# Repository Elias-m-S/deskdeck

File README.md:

<h1 align="center">DeskDeck</h1>

<p align="center">
  <b>An ESP32-S3 macro pad that lives under the edge of your desk:</b><br>
  per-app volume knobs, a sit/stand desk controller with a laser height sensor, and a Home Assistant link.<br>
  Firmware, PCB and 3D-printed enclosure, all in one repository.
</p>

<p align="center">

</p>

---

## What it does

- **Per-app volume on two knobs.** Each EC11 encoder is bound to an application (Discord, a game, the browser, the master output). A small host daemon talks to PipeWire/PulseAudio over the USB serial port; the OLED shows name, level and a bar for each knob. Press a knob to mute. Without the daemon, the master knob still works through plain USB media keys.
- **Four MX keys.** Keyboard shortcuts over USB HID (e.g. `Super+1`), or special actions: one key toggles the desk between sitting and standing, one triggers a light scene in Home Assistant.
- **Sit/stand desk controller.** Two optocouplers sit in parallel with the desk's own buttons, galvanically isolated from the ESP. A VL53L1X time-of-flight sensor measures the height to the floor. Profiles, calibration and the learned coasting distance are stored in flash. The drive logic is a pure state machine with hard safety limits and a host-side simulation test.
- **Home Assistant over Wi-Fi + MQTT.** The device announces itself through MQTT discovery: a desk-height sensor, sit/stand buttons and a key trigger. HA can push short messages to the display.
- **No buttons needed to flash.** The firmware reboots itself into the ROM bootloader on request; `flash.sh` builds, flashes and restarts in one go.
- **Two mechanical desk buttons** on the same board are wired straight to the desk, so the desk always works, even with the ESP unpowered.

## Gallery

| PCB, bottom side (ESP32-S3 SuperMini, optocouplers, terminal block) | Schematic |
|---|---|
|  |  |

| Enclosure, exploded | Section through display, encoder and keys |
|---|---|
|  |  |

| Two-colour keycaps (3MF, generated from Lucide icons) |
|---|
|  |

## How it works

```mermaid
flowchart LR
    subgraph DeskDeck["DeskDeck (ESP32-S3, FreeRTOS)"]
        direction LR
        IN[input<br/>keys + encoders<br/>PCNT, debounce] -->|events| UI[ui<br/>state machine<br/>menus, NVS]
        UI --> HID[usb_hid<br/>keyboard + media keys]
        UI --> HL[host_link<br/>text protocol over CDC]
        UI --> DISP[display<br/>SH1106 128x64]
        TOF[tof<br/>VL53L1X 20 Hz] --> DESK[desk<br/>drive logic + safety]
        UI --> DESK
        HA[ha_link<br/>Wi-Fi + MQTT]
        HA <--> UI
        DESK --> HA
    end
    HID -->|USB HID| PC[(PC)]
    HL <-->|USB CDC| DAEMON[host daemon<br/>pactl / PipeWire]
    DAEMON --- PC
    DESK -->|2x PC817| MOTOR[desk control box]
    HA <-->|MQTT| HASS[Home Assistant]
```

Every block is its own FreeRTOS task. All UI state belongs to exactly one task and is fed through a single event queue, so there is no shared mutable state to lock.

**Per-app volume.** The device sends `@ADJ +2 Discord` or `@MUTE Discord` over the CDC port. The daemon matches the name against running audio streams (`application.name` / binary) and applies it with `pactl`; it answers with `@LVL <percent> <muted> <active> <name>` and the list of selectable targets, which the device shows in its menu. Levels for apps that are not running are remembered and applied as soon as a stream appears. Protocol: [`firmware/main/host_link.h`](firmware/main/host_link.h).

**Desk control.** Target height = sensor distance + calibrated offset. The logic in [`desk_logic.c`](firmware/main/desk_logic.c) has no hardware access and is exercised against a simulated desk in [`test/desk_sim.c`](firmware/test/desk_sim.c): accuracy after learning the coasting distance, plus every abort case. Safety rules:

| Rule | Value |
|---|---|
| Maximum time per profile move | 20 s |
| After a 2 s spin-up the desk must move per second at least | 8 mm in the right direction |
| Movement in the wrong direction aborts after | 15 mm |
| No fresh sensor reading for | 300 ms -> abort |
| Any user input while moving | stops immediately |
| Outputs | off at boot, never both on at once, pulled down in hardware |

**Home Assistant.** MQTT discovery creates a device *DeskDeck* with the entities desk height (`deskdeck/desk/height`), sit/stand buttons (`deskdeck/cmd/desk`) and a trigger for key 4 (`deskdeck/key/4`). `deskdeck/cmd/toast` shows a short text on the display. Topics: [`firmware/main/ha_link.h`](firmware/main/ha_link.h).

## Repository layout

| Directory | Contents | Details |
|---|---|---|
| [`firmware/`](firmware/) | ESP-IDF project: input, UI, display driver, VL53L1X driver, desk logic, USB composite device, MQTT | [firmware/README.md](firmware/README.md) |
| [`host/`](host/) | Python daemon for per-app volume (PipeWire/PulseAudio via `pactl`), systemd user unit | [host/README.md](host/README.md) |
| [`hardware/`](hardware/) | KiCad project, Gerber ZIP for JLCPCB, BOM, schematic PDF, Python generator that builds schematic + board from one data file | [hardware/README.md](hardware/README.md) |
| [`enclosure/`](enclosure/) | Parametric FreeCAD enclosure (reads the board data from `hardware/`), print-ready STL, two-colour keycaps | [enclosure/README.md](enclosure/README.md) |
| [`docs/images/`](docs/images/) | Renders used in the READMEs | |

## Build one

1. **PCB.** Upload [`hardware/fabrication/deskdeck-gerber-jlcpcb.zip`](hardware/fabrication/) to JLCPCB or any 2-layer fab (119 x 62 mm, 1.6 mm, HASL). Parts are all through-hole, see the [BOM](hardware/fabrication/bom.csv) and the [soldering order](hardware/README.md#assembly-order).
2. **Enclosure.** Print the five STL files in [`enclosure/stl/`](enclosure/stl/) (PETG, no supports) and the keycaps in [`enclosure/keycaps/`](enclosure/keycaps/). Assembly and the drill template for the desk are in [enclosure/README.md](enclosure/README.md).
3. **Firmware.**
   ```bash
   cd firmware
   cp main/secrets.h.example main/secrets.h   # Wi-Fi/MQTT credentials, or leave empty
   idf.py set-target esp32s3 && idf.py build
   ./flash.sh                                   # or: idf.py flash
   ```
   First flash of a blank board: hold BOOT, tap RST, release BOOT, then flash. From then on `flash.sh` reboots the device into the bootloader by itself.
4. **Host daemon** (Linux with PipeWire or PulseAudio):
   ```bash
   sudo apt install python3-serial pulseaudio-utils
   host/install.sh                              # systemd user service, starts at login
   ```
   Then edit `~/.config/deskdeck/config.json` to map knob targets to your applications (`host/deskdeck_daemon.py --list` shows what is playing).
5. **Home Assistant.** Point `MQTT_URI` in `secrets.h` at your broker. The device appears automatically. Create an automation on the key-4 trigger and, optionally, publish feedback to `deskdeck/cmd/toast`.

## Hardware at a glance

| Part | Role |
|---|---|
| ESP32-S3 SuperMini | MCU, native USB (TinyUSB composite: HID + CDC), Wi-Fi |
| 1.3" SH1106 OLED, I2C | Display, flush with the lid |
| 2x EC11 rotary encoder with push button | Volume / menu, mute |
| 6x Cherry MX compatible switches | 4 macro keys + 2 purely mechanical desk buttons |
| VL53L1X (TOF400C module) | Height to the floor, 20 Hz, median filtered, narrowed ROI |
| 2x PC817 optocoupler, 470 R + 10 k | Isolated desk UP/DOWN outputs |
| 3-pole screw terminal | Desk control box (VCC, M1, M2) |

Pin map (all inputs active-low with internal pull-ups):

| Function | GPIO |
|---|---|
| Encoder 1 A / B / switch | 1 / 2 / 4 |
| Encoder 2 A / B / switch | 9 / 10 / 11 |
| MX keys 1-4 | 5, 6, 7, 8 |
| I2C SDA / SCL (OLED + sensor) | 12 / 13 |
| Desk UP / DOWN (optocoupler LEDs) | 44 / 3 |
| On-board WS2812 status LED | 48 |

Everything configurable (pins, key map, encoder targets, desk limits, timings) lives in [`firmware/main/config.h`](firmware/main/config.h).

## Safety

The desk side of the board carries the desk's own control voltage. It is isolated from the ESP by the optocouplers, a copper keep-out and a DRC rule enforcing 0.8 mm clearance; there is no shared ground. Keep it that way. Start with `DESK_DRY_RUN 1` in `config.h`: the complete logic runs, including the sensor, but the outputs never switch. Only after you have verified the wiring, set it to `0` and calibrate the height once from the menu.

## Notes

- The strings shown on the OLED and the Home Assistant entity names are German, the author's UI language. They are plain literals in `ui.c`, `desk_logic.c`, `tof.c` and `ha_link.c`.
- Mechanical dimensions (SuperMini footprint, OLED module, TOF400C cap, EC11 clone body) were measured on the actual parts; the READMEs list what to re-measure before ordering or printing.
- Boards fabricated before the project was renamed carry the silkscreen "ESP32-S3 Stream Deck v2". They are electrically identical to this revision.

## License

MIT, see [LICENSE](LICENSE). It also lists the third-party pieces: the Adafruit 5x7 font, the register sequence from ST's VL53L1X Ultra Lite Driver, Lucide icon outlines on the keycaps, and symbols/footprints from the KiCad libraries.

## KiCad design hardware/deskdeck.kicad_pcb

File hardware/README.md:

# PCB (rev 2)

2-layer board, **119 x 62 mm**, through-hole parts only (everything is hand-solderable). KiCad 7 format, opens in KiCad 7 to 10 (newer versions ask to convert once).

| Bottom side | Top side |
|---|---|
|  |  |

```
Top side                                           Bottom side (top strip + behind the OLED)
┌──────────────────────────────────────────┐       ESP32-S3 SuperMini on female headers (USB-C towards the top
│ ┌────────┐ (E1)  [1]  [3]  [▲]            │       edge, BOOT/RST reachable from the back), 2x PC817, 4 resistors,
│ │  OLED  │                                │       sensor header (1x4), desk screw terminal (3-pole)
│ └────────┘ (E2)  [2]  [4]  [▼]            │
└──────────────────────────────────────────┘
```

## Desk interface

The desk switches **high side**: the original hand switch connects `VCC` to `M1` (up) or `M2` (down). The desk buttons ▲▼ and the optocoupler outputs sit **in parallel** on these lines, so the buttons always work, even without the ESP.

| Terminal J3 | Desk line | PC817 | Button |
|---|---|---|---|
| 1 `UP` | M1 | U2 pin 3 (emitter) | SW7 |
| 2 `DOWN` | M2 | U3 pin 3 (emitter) | SW8 |
| 3 `VCC` | VCC | U2 + U3 pin 4 (collector) | SW7 + SW8 |

The nets `DESK_UP`, `DESK_DN`, `DESK_VCC` are **galvanically isolated from the ESP**. They belong to the net class `Desk`, and the DRC rule in `deskdeck.kicad_dru` demands **>= 0.8 mm** clearance to everything on the ESP side. There is deliberately no GND pour in the desk area.

rev 1 -> rev 2: `DESK_GND` -> `DESK_VCC`, pins 3 and 4 swapped on U2/U3, isolation clearance 0.25 -> 0.8 mm, silkscreen with >= 0.15 mm line width.

## Verification status (rev 2)

- Schematic netlist, board and `generator/design.py` compared automatically (`generator/check.py`): **identical**
- DRC: **0 unconnected items, 0 clearance, courtyard or silkscreen errors** (tracks 0.3 mm, clearance 0.25 mm, vias 0.7/0.35 mm). KiCad 8+ additionally reports the SuperMini socket pins inside the OLED courtyard, which is intentional: those pins are clipped flush, see the assembly order.
- Isolation clearance desk <-> ESP measured (`generator/iso.py`): **0.80 mm**
- GPIOs cross-checked against `firmware/main/config.h`: encoders 1/2/4 and 9/10/11, keys 5-8, I2C 12/13, desk 44/3
- Gerbers rendered independently and inspected; drill files separated (PTH/NPTH)
- Tested on a breadboard: optocouplers, desk buttons in parallel, manual drive
- Measured on the real parts: SuperMini pinout (`TX RX 1-7` / `5V GND 3V3 13-8`, USB up), row pitch ~15.2 mm, OLED pins `GND VCC SCL SDA`

## Ordering (JLCPCB or similar)

1. Upload `fabrication/deskdeck-gerber-jlcpcb.zip`
2. Defaults: 2 layers, 1.6 mm, HASL, any colour
3. The size is detected from the file (119 x 62 mm)

## Parts

See [`fabrication/bom.csv`](fabrication/bom.csv). Apart from the modules (SuperMini, OLED, TOF400C, encoders, switches) you only need small parts: 2x female header 1x9, 2x pin header 1x4 (OLED + sensor), 3-pole screw terminal 5.08 mm, 2x 470 R, 2x 10 k, M3 screws/stand-offs.

## Assembly order

Flat parts first so the board lies flat while soldering:

1. **Bottom side:** resistors R1-R4 -> PC817 (notch/dot = pin 1, see silkscreen) -> pin header J2 -> screw terminal J3 (cable entry towards the top edge)
2. **Bottom side:** 1x9 female headers for the SuperMini. Tip: keep the module plugged in while soldering the headers, then they sit straight.
3. **Top side, under the OLED:** clip the 6 lowest pins of the SuperMini headers (the bottom 3 of each row) flush and cover the spot with Kapton tape. The OLED later sits only ~2.5 mm above the board.
4. **Top side:** solder the OLED **directly** (no socket, so the glass ends up flush with the lid): a normal 1x4 pin header, plastic spacer resting on the board, clip the short pin ends flush on top of the OLED. Align the OLED level, solder one pin, check, then the rest.
5. **Top side:** encoders, finally the MX switches (best with the lid clipped on as a switch plate, then they sit exactly)

**Desk cable:** 3 wires to J3: `UP` = M1, `DOWN` = M2, `VCC` = desk VCC.
**Sensor:** 4-wire cable from J2 to the TOF400C, by label: `3V3`->`VIN`, `GND`->`GND`, `SDA`->`SDA`, `SCL`->`SCL`.

## Files

```
deskdeck.*        KiCad project (schematic, board, project symbol/footprint libraries)
fabrication/      Gerber ZIP, schematic PDF, BOM
generator/        Python scripts that generate schematic + board from design.py (KiCad 7 + Freerouting)
```

The enclosure ([`../enclosure/`](../enclosure/)) imports `generator/design.py` for the board outline, holes and part positions.

### Generator

`design.py` holds the circuit as data: parts, footprints, positions and the pin-to-net map. `gen_sch.py` and `gen_pcb.py` turn it into a schematic and an unrouted board (so both match by construction), `route.py` runs Freerouting and imports the result with GND pours, `check.py` runs DRC and compares schematic, board and `design.py`, `iso.py` measures the isolation clearance. `gen_pcb.py`/`route.py` use the KiCad 7 pcbnew Python API. If you continue by hand in KiCad, the KiCad files are the source from then on, not `design.py`.

Boards fabricated before the project was renamed carry the silkscreen "ESP32-S3 Stream Deck v2"; the copper is identical.

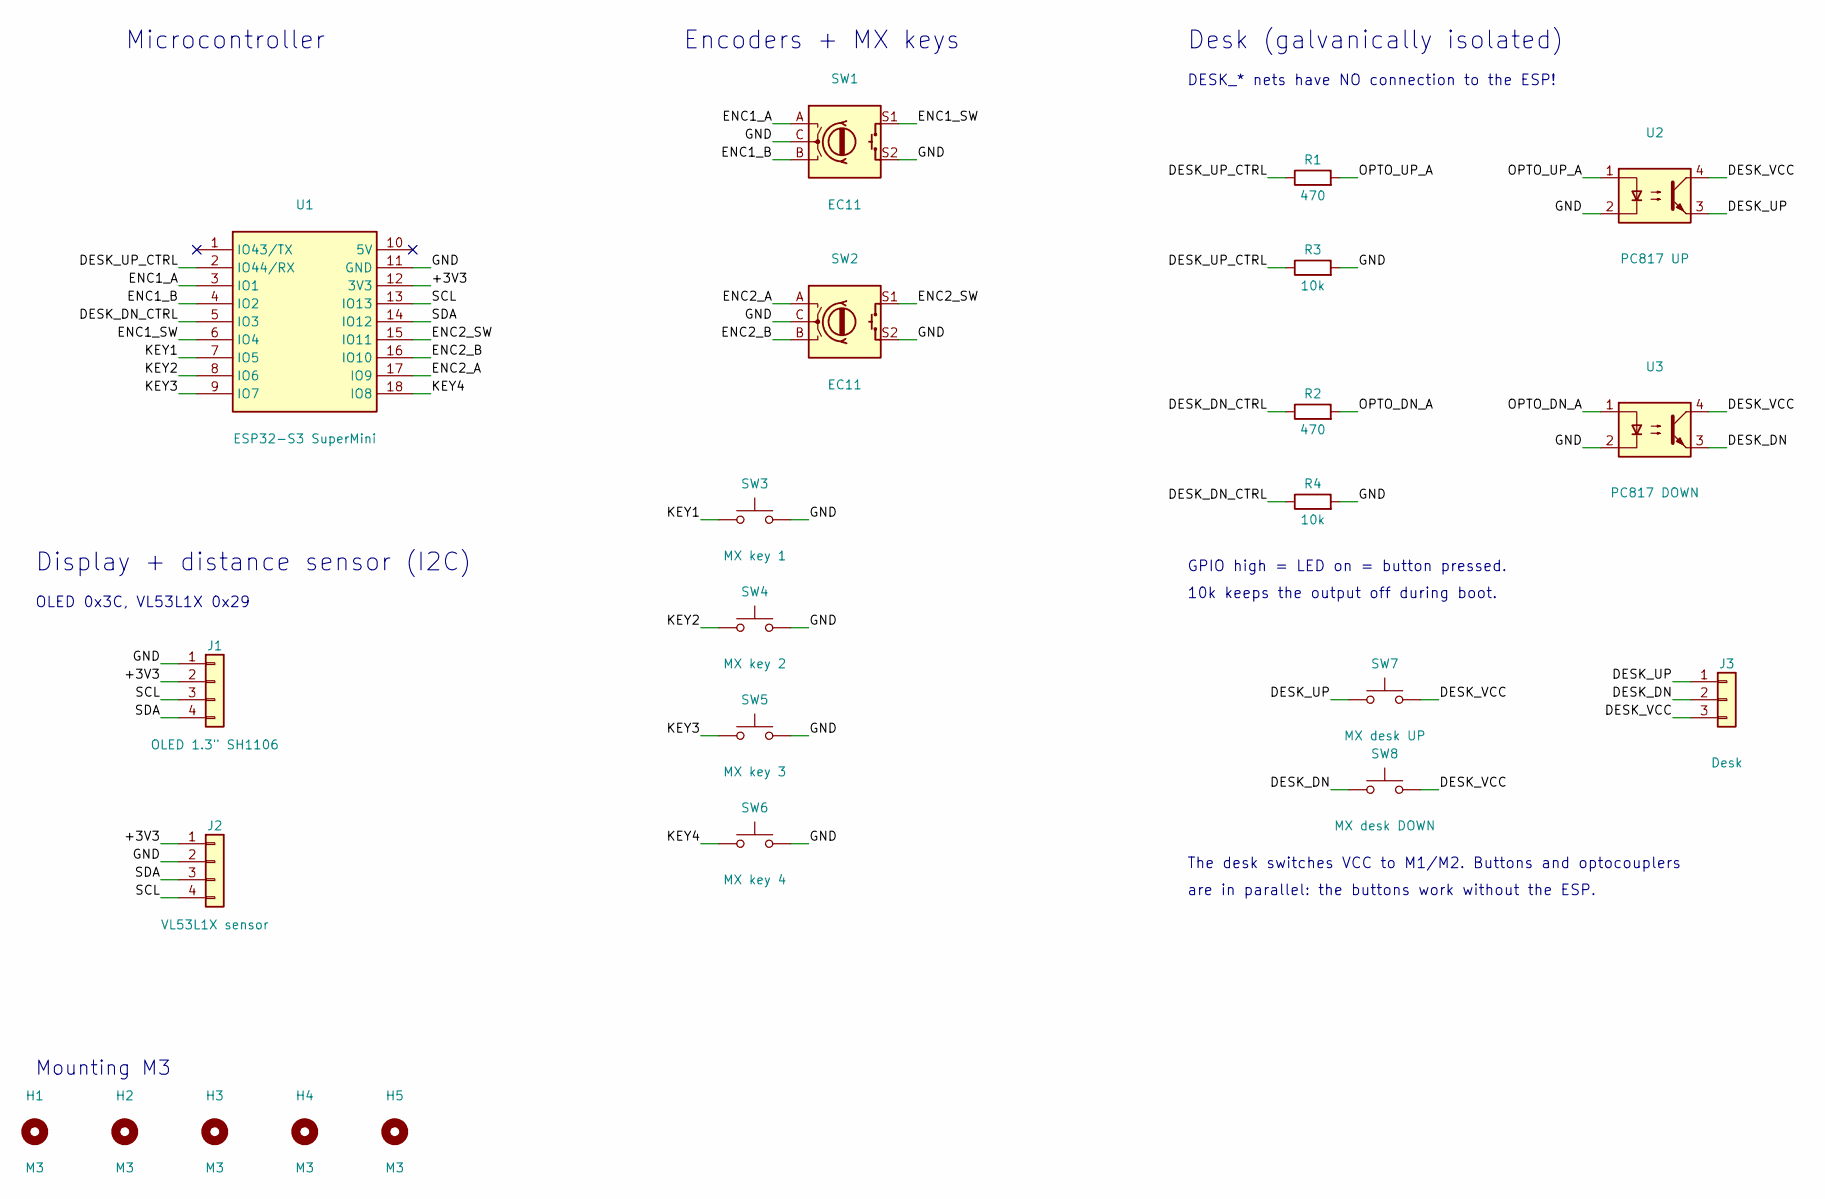
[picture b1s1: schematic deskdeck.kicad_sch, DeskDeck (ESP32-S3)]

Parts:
H1, H2, H3, H4, H5: M3; MountingHole_3.2mm_M3
J1: OLED 1.3" SH1106; OLED_1.3in_I2C_Socket
J2: VL53L1X sensor; PinHeader_1x04_P2.54mm_Vertical
J3: Desk; TerminalBlock_Phoenix_MKDS-1,5-3-5.08_1x03_P5.08mm_Horizont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
R1, R2: 470; R_Axial_DIN0207_L6.3mm_D2.5mm_P7.62mm_Horizontal
R3, R4: 10k; R_Axial_DIN0207_L6.3mm_D2.5mm_P7.62mm_Horizontal
SW1, SW2: EC11; RotaryEncoder_Alps_EC11E-Switch_Vertical_H20mm
SW3: MX key 1; SW_Cherry_MX_1.00u_PCB
SW4: MX key 2; SW_Cherry_MX_1.00u_PCB
SW5: MX key 3; SW_Cherry_MX_1.00u_PCB
SW6: MX key 4; SW_Cherry_MX_1.00u_PCB
SW7: MX desk UP; SW_Cherry_MX_1.00u_PCB
SW8: MX desk DOWN; SW_Cherry_MX_1.00u_PCB
U1: ESP32-S3 SuperMini; ESP32-S3_SuperMini_Socket
U2: PC817 UP; DIP-4_W7.62mm
U3: PC817 DOWN; DIP-4_W7.62mm

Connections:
+3V3: J1.2, J2.1, U1.12 (3V3)
DESK_DN: J3.2, SW8.1, U3.3
DESK_DN_CTRL: R2.1, R4.1, U1.5 (IO3)
DESK_UP: J3.1, SW7.1, U2.3
DESK_UP_CTRL: R1.1, R3.1, U1.2 (IO44/RX)
DESK_VCC: J3.3, SW7.2, SW8.2, U2.4, U3.4
ENC1_A: SW1.A, U1.3 (IO1)
ENC1_B: SW1.B, U1.4 (IO2)
ENC1_SW: SW1.S1, U1.6 (IO4)
ENC2_A: SW2.A, U1.17 (IO9)
ENC2_B: SW2.B, U1.16 (IO10)
ENC2_SW: SW2.S1, U1.15 (IO11)
GND: J1.1, J2.2, R3.2, R4.2, SW1.C, SW1.S2, SW2.C, SW2.S2, SW3.2, SW4.2, SW5.2, SW6.2, U1.11 (GND), U2.2, U3.2
KEY1: SW3.1, U1.7 (IO5)
KEY2: SW4.1, U1.8 (IO6)
KEY3: SW5.1, U1.9 (IO7)
KEY4: SW6.1, U1.18 (IO8)
OPTO_DN_A: R2.2, U3.1
OPTO_UP_A: R1.2, U2.1
SCL: J1.3, J2.4, U1.13 (IO13)
SDA: J1.4, J2.3, U1.14 (IO12)

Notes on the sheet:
Microcontroller
Display + distance sensor (I2C)
OLED 0x3C, VL53L1X 0x29
Encoders + MX keys
Desk (galvanically isolated)
DESK_* nets have NO connection to the ESP!
GPIO high = LED on = button pressed.
10k keeps the output off during boot.
The desk switches VCC to M1/M2. Buttons and optocouplers
are in parallel: the buttons work without the ESP.
Mounting M3

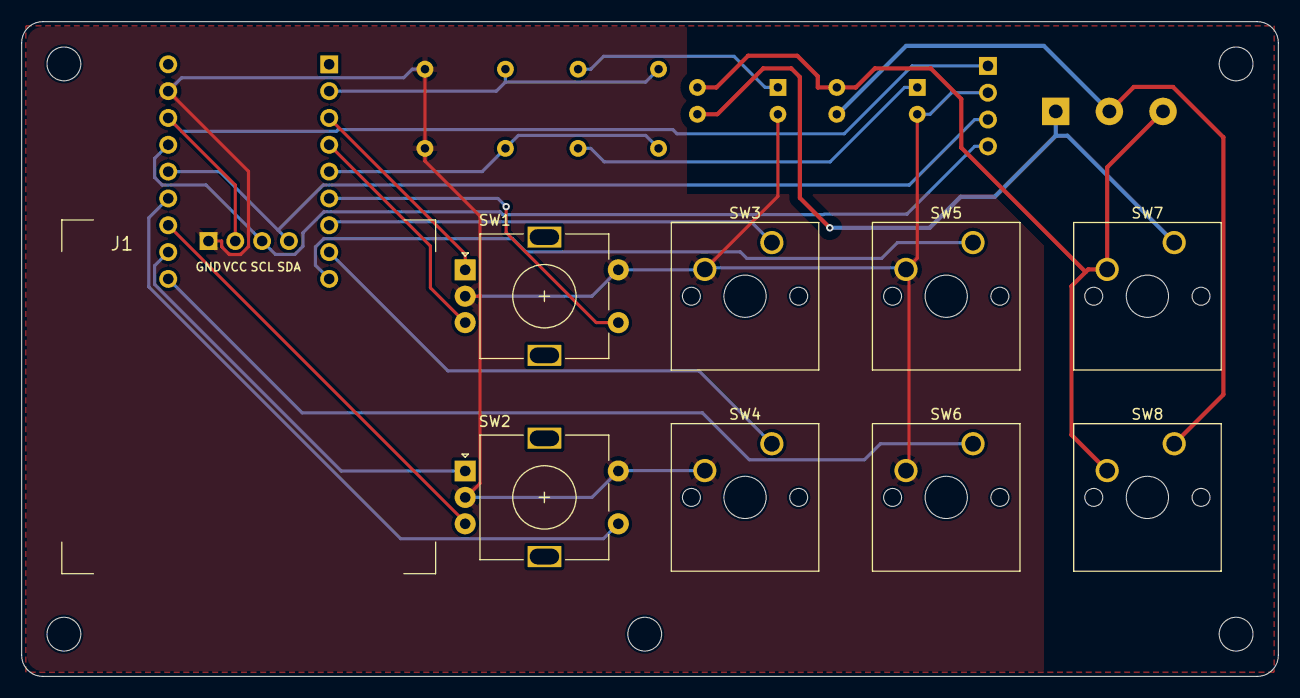
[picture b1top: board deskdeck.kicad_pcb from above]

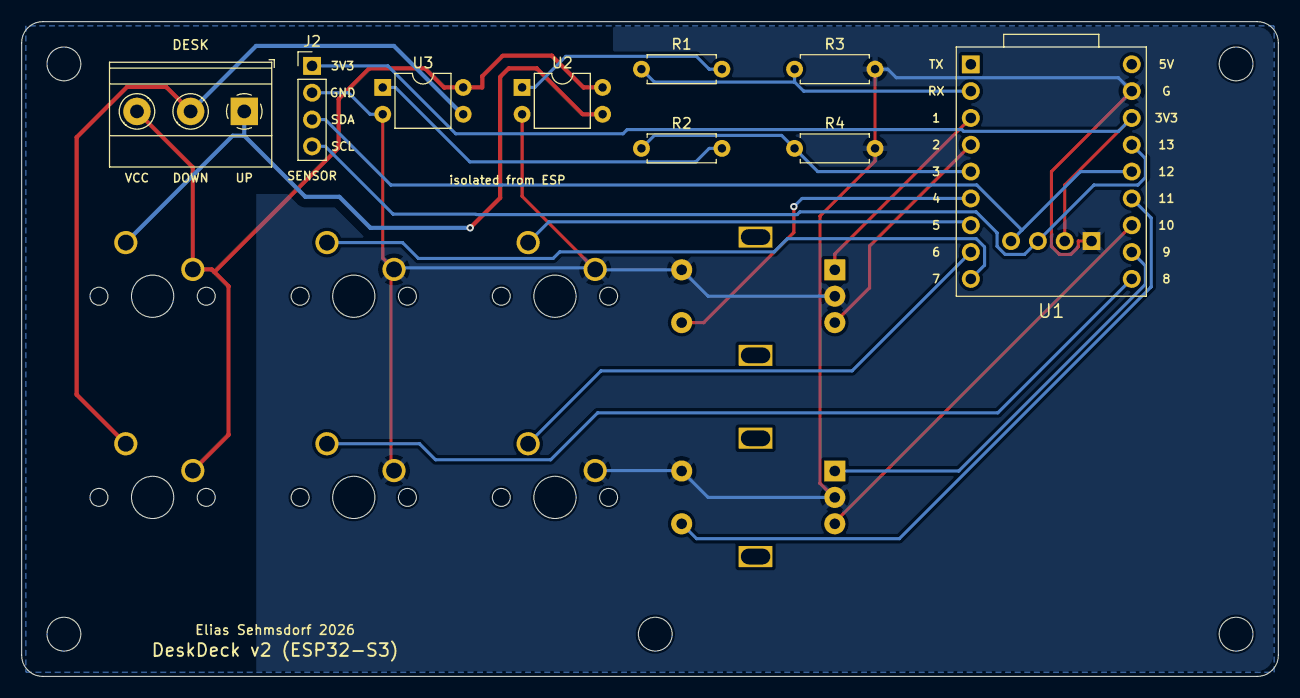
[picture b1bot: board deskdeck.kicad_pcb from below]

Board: 2 copper layers, 119.0 x 62.0 mm, 23 parts (9 on the bottom side), 21 nets.
